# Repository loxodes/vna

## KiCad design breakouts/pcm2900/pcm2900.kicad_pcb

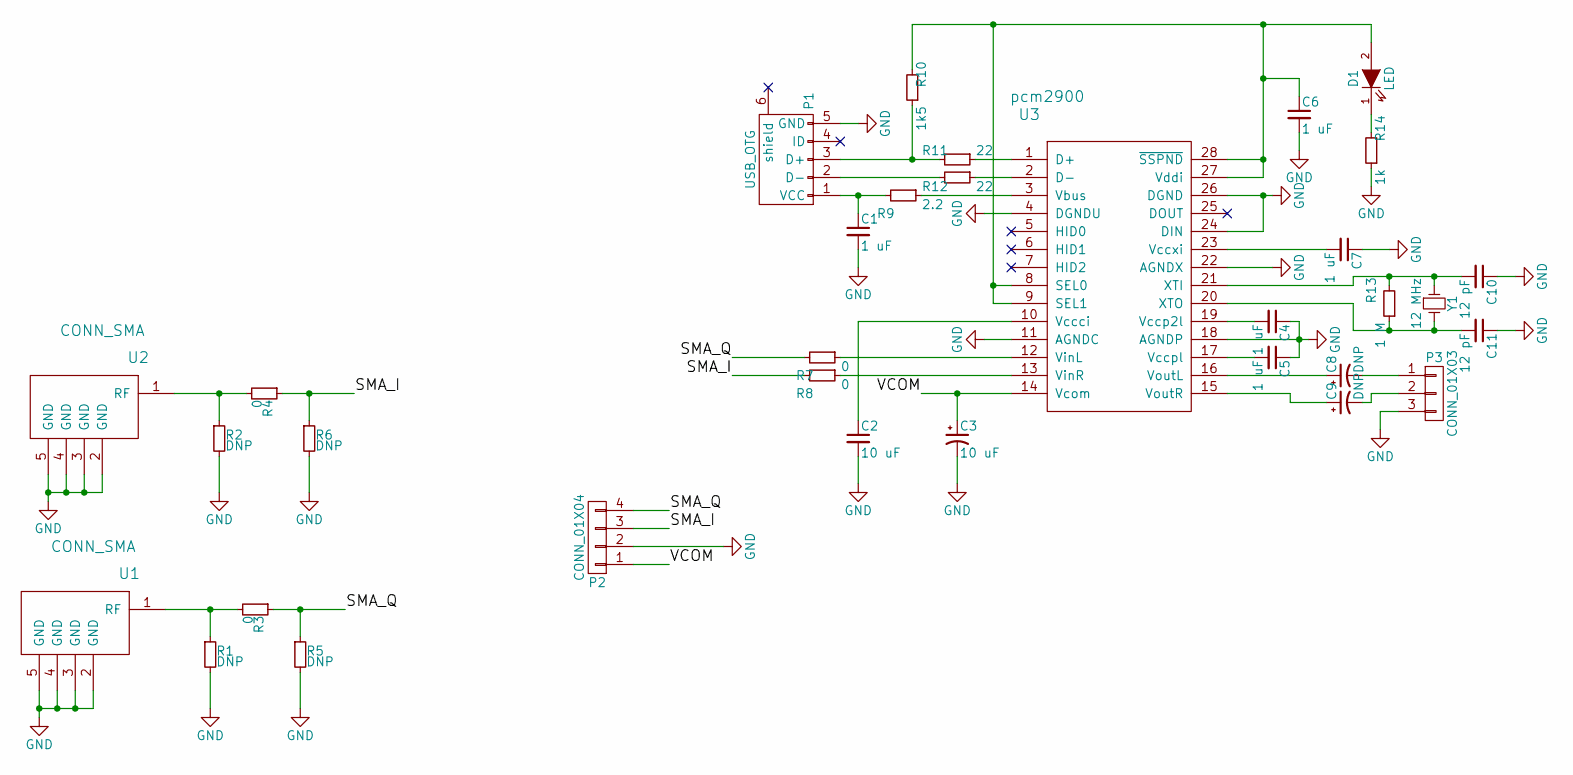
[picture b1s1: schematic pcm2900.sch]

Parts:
C1, C4, C5, C6, C7: 1 uF; C_0603
C2, C3: 10 uF; TantalC_SizeA_EIA-3216_Wave
C8, C9: DNP; TantalC_SizeA_EIA-3216_Wave
C10, C11: 12 pF; C_0603
D1: LED; LED_0603
P1: USB_OTG; USB_Mini-B
P2: CONN_01X04; Pin_Header_Straight_1x04
P3: CONN_01X03; Pin_Header_Straight_1x03
R1, R2, R5, R6: DNP; R_0603
R3, R4: 0; R_0603
R7, R8: 0; R_0805
R9: 2.2; R_0603
R10: 1k5; R_0603
R11, R12: 22; R_0603
R13: 1 M; R_0603
R14: 1k; R_0603
U1, U2: CONN_SMA; 732512200_SMA
U3: pcm2900; SSOP-28_5.3x10.2mm_Pitch0.65mm
Y1: 12 MHz; Crystal_FOX-FE_SMD

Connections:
/SMA_I: P2.3, R4.1, R6.1, R8.2
/SMA_Q: P2.4, R3.1, R5.1, R7.2
/VCOM: C3.1, P2.1, U3.14 (Vcom)
GND: C1.2, C2.2, C3.2, C4.1, C5.1, C6.2, C7.1, C10.1, C11.1, P1.5 (GND), P2.2, P3.3, R1.2, R2.2, R5.2, R6.2, R14.1, U1.2 (GND), U1.3 (GND), U1.4 (GND), U1.5 (GND), U2.2 (GND), U2.3 (GND), U2.4 (GND), U2.5 (GND), U3.4 (DGNDU), U3.11 (AGNDC), U3.18 (AGNDP), U3.22 (AGNDX), U3.24 (DIN), U3.26 (DGND)
unnamed: C1.1, P1.1 (VCC), R9.2
unnamed: C2.1, U3.10 (Vccci)
unnamed: C4.2, U3.19 (Vccp2l)
unnamed: C5.2, U3.17 (Vccpl)
unnamed: C6.1, D1.2 (A), R10.2, U3.8 (SEL0), U3.9 (SEL1), U3.27 (Vddi), U3.28 (~SSPND)
unnamed: C7.2, U3.23 (Vccxi)
unnamed: C8.1, U3.16 (VoutL)
unnamed: C8.2, P3.1
unnamed: C9.1, U3.15 (VoutR)
unnamed: C9.2, P3.2
unnamed: C10.2, R13.2, U3.21 (XTI), Y1.1
unnamed: C11.2, R13.1, U3.20 (XTO), Y1.2
unnamed: D1.1 (K), R14.2
unnamed: P1.2 (D-), R12.2
unnamed: P1.3 (D+), R10.1, R11.2
unnamed: R1.1, R3.2, U1.1 (RF)
unnamed: R2.1, R4.2, U2.1 (RF)
unnamed: R7.1, U3.12 (VinL)
unnamed: R8.1, U3.13 (VinR)
unnamed: R9.1, U3.3 (Vbus)
unnamed: R11.1, U3.1 (D+)
unnamed: R12.1, U3.2 (D-)

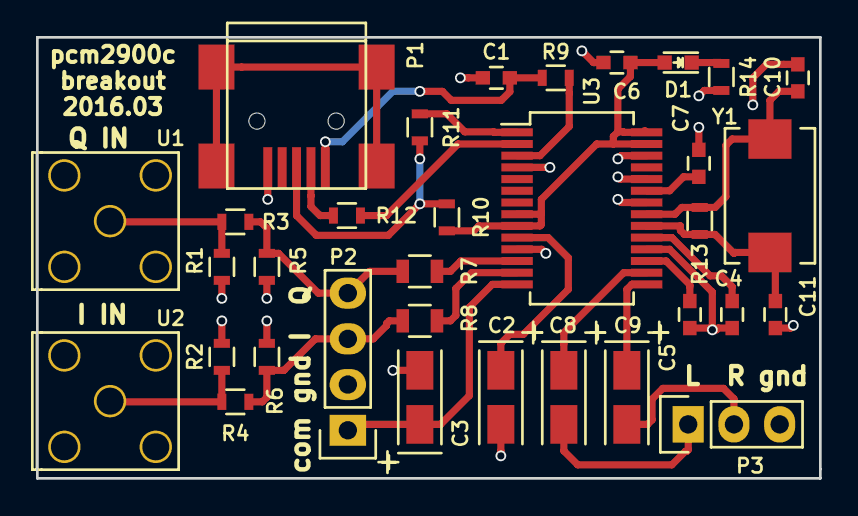
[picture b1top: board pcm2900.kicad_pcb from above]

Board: 2 copper layers, 43.5 x 24.5 mm, 33 parts (0 on the bottom side), 26 nets.

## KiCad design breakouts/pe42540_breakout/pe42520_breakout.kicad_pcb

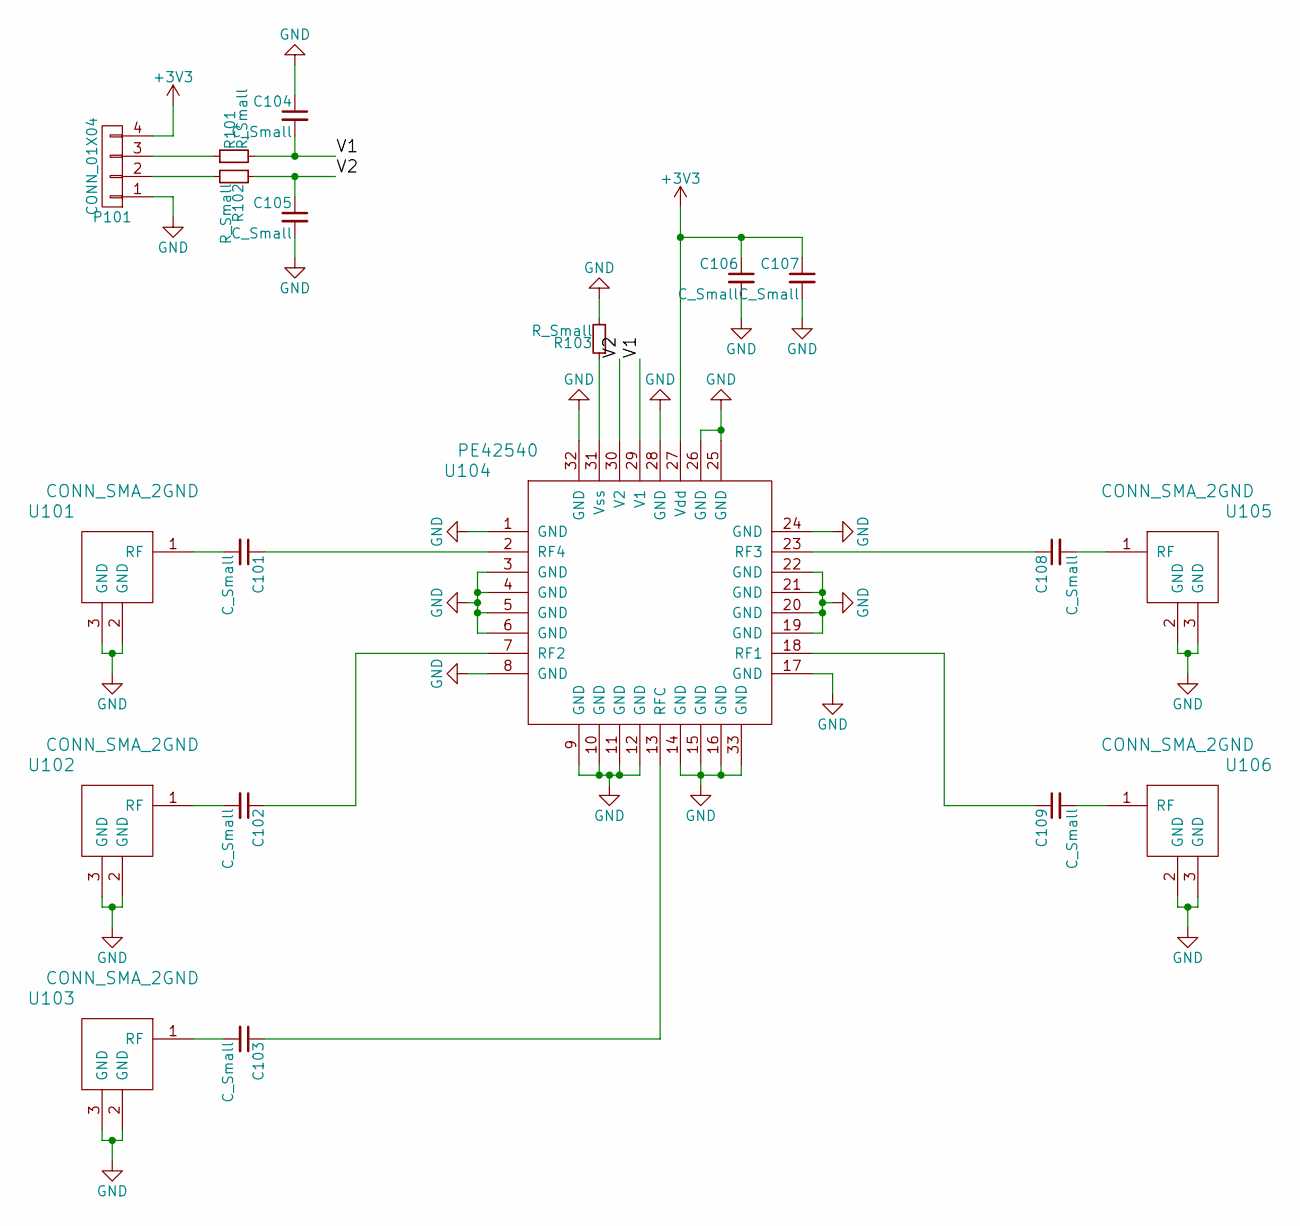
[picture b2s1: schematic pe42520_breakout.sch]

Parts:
C101, C102, C103, C104, C105, C106, C107, C108, C109: C_Small; C_0402
P101: CONN_01X04; Pin_Header_Angled_1x04
R101, R102, R103: R_Small; R_0402
U101, U102, U103, U105, U106: CONN_SMA_2GND; SMA_CPW_1MM_.2MM
U104: PE42540; LGA_32

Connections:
+3V3: C106.1, C107.1, P101.4, U104.27 (Vdd)
/V1: C104.2, R101.2, U104.29 (V1)
/V2: C105.1, R102.1, U104.30 (V2)
GND: C104.1, C105.2, C106.2, C107.2, P101.1, R103.2, U101.2 (GND), U101.3 (GND), U102.2 (GND), U102.3 (GND), U103.2 (GND), U103.3 (GND), U104.1 (GND), U104.3 (GND), U104.4 (GND), U104.5 (GND), U104.6 (GND), U104.8 (GND), U104.9 (GND), U104.10 (GND), U104.11 (GND), U104.12 (GND), U104.14 (GND), U104.15 (GND), U104.16 (GND), U104.17 (GND), U104.19 (GND), U104.20 (GND), U104.21 (GND), U104.22 (GND), U104.24 (GND), U104.25 (GND), U104.26 (GND), U104.28 (GND), U104.32 (GND), U104.33 (GND), U105.2 (GND), U105.3 (GND), U106.2 (GND), U106.3 (GND)
unnamed: C101.1, U104.2 (RF4)
unnamed: C101.2, U101.1 (RF)
unnamed: C102.1, U104.7 (RF2)
unnamed: C102.2, U102.1 (RF)
unnamed: C103.1, U104.13 (RFC)
unnamed: C103.2, U103.1 (RF)
unnamed: C108.1, U104.23 (RF3)
unnamed: C108.2, U105.1 (RF)
unnamed: C109.1, U104.18 (RF1)
unnamed: C109.2, U106.1 (RF)
unnamed: P101.2, R102.2
unnamed: P101.3, R101.1
unnamed: R103.1, U104.31 (Vss)

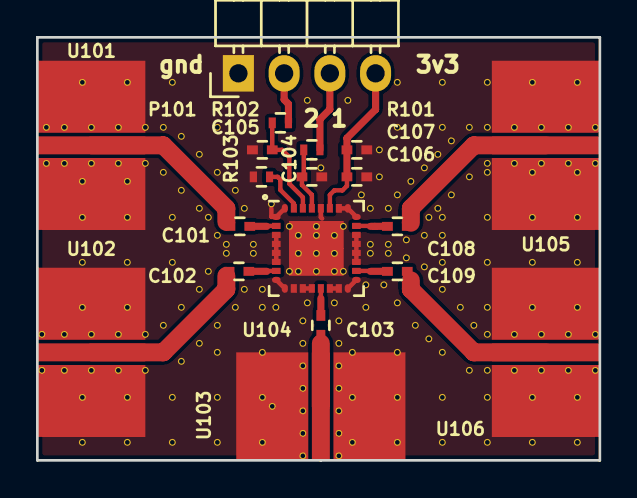
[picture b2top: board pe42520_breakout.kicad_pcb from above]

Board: 4 copper layers, 31.2 x 23.5 mm, 19 parts (0 on the bottom side), 17 nets.

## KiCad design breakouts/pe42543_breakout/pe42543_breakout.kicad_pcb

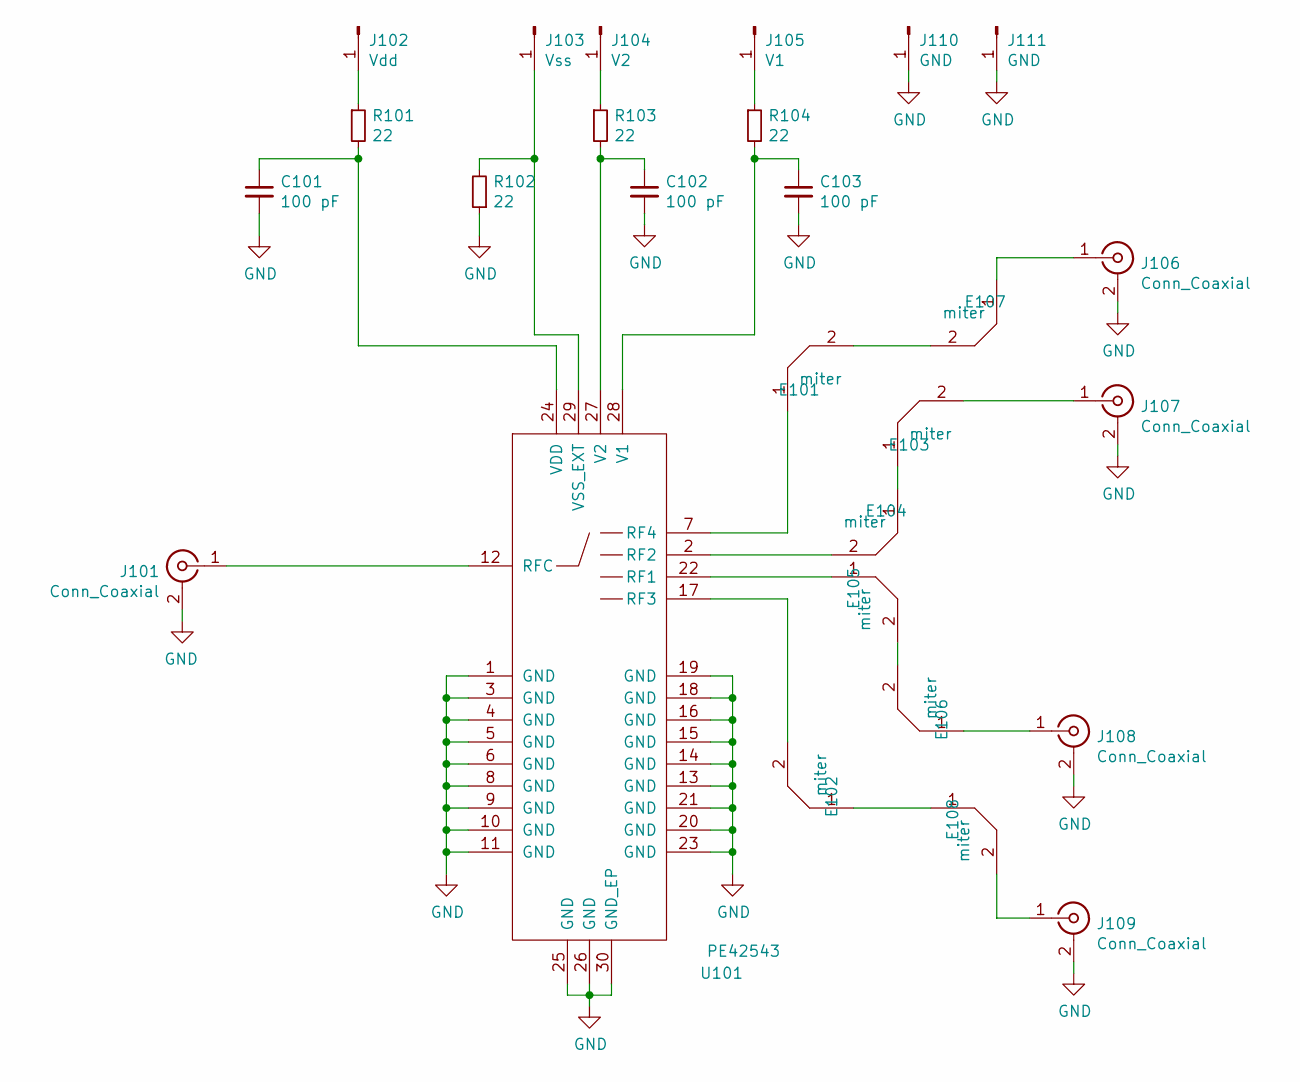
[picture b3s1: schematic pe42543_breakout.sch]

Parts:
C101, C102, C103: 100 pF; C_0402
E101, E102, E103, E104, E105, E106, E107, E108: miter; p41mm_miter
J101, J106, J107, J108, J109: Conn_Coaxial; sw_edge_oshpark_4layer
J102: Vdd; TURRET_MILLMAX_2101
J103: Vss; TURRET_MILLMAX_2101
J104: V2; TURRET_MILLMAX_2101
J105: V1; TURRET_MILLMAX_2101
J110, J111: GND; TURRET_MILLMAX_2101
R101, R102, R103, R104: 22; R_0402
U101: PE42543; RFSW__PE42543A-X

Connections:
GND: C101.2, C102.2, C103.2, J101.2 (Ext), J106.2 (Ext), J107.2 (Ext), J108.2 (Ext), J109.2 (Ext), J110.1, J111.1, R102.1, U101.1 (GND), U101.3 (GND), U101.4 (GND), U101.5 (GND), U101.6 (GND), U101.8 (GND), U101.9 (GND), U101.10 (GND), U101.11 (GND), U101.13 (GND), U101.14 (GND), U101.15 (GND), U101.16 (GND), U101.18 (GND), U101.19 (GND), U101.20 (GND), U101.21 (GND), U101.23 (GND), U101.25 (GND), U101.26 (GND), U101.30 (GND_EP)
unnamed: C101.1, R101.2, U101.24 (VDD)
unnamed: C102.1, R103.2, U101.27 (V2)
unnamed: C103.1, R104.2, U101.28 (V1)
unnamed: E101.1, U101.7 (RF4)
unnamed: E101.2, E107.2
unnamed: E102.1, E108.1
unnamed: E102.2, U101.17 (RF3)
unnamed: E103.1, E104.1
unnamed: E103.2, J107.1 (In)
unnamed: E104.2, U101.2 (RF2)
unnamed: E105.1, U101.22 (RF1)
unnamed: E105.2, E106.2
unnamed: E106.1, J108.1 (In)
unnamed: E107.1, J106.1 (In)
unnamed: E108.2, J109.1 (In)
unnamed: J101.1 (In), U101.12 (RFC)
unnamed: J102.1, R101.1
unnamed: J103.1, R102.2, U101.29 (VSS_EXT)
unnamed: J104.1, R103.1
unnamed: J105.1, R104.1

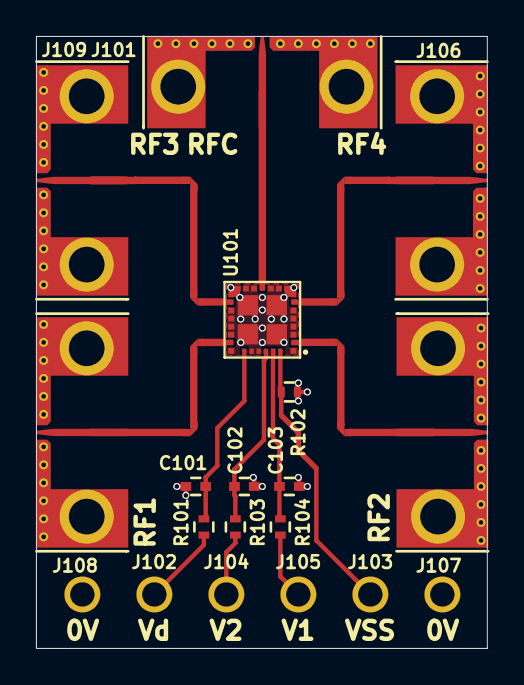
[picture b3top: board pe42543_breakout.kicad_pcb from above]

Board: 4 copper layers, 25.1 x 34.0 mm, 27 parts (0 on the bottom side), 21 nets.

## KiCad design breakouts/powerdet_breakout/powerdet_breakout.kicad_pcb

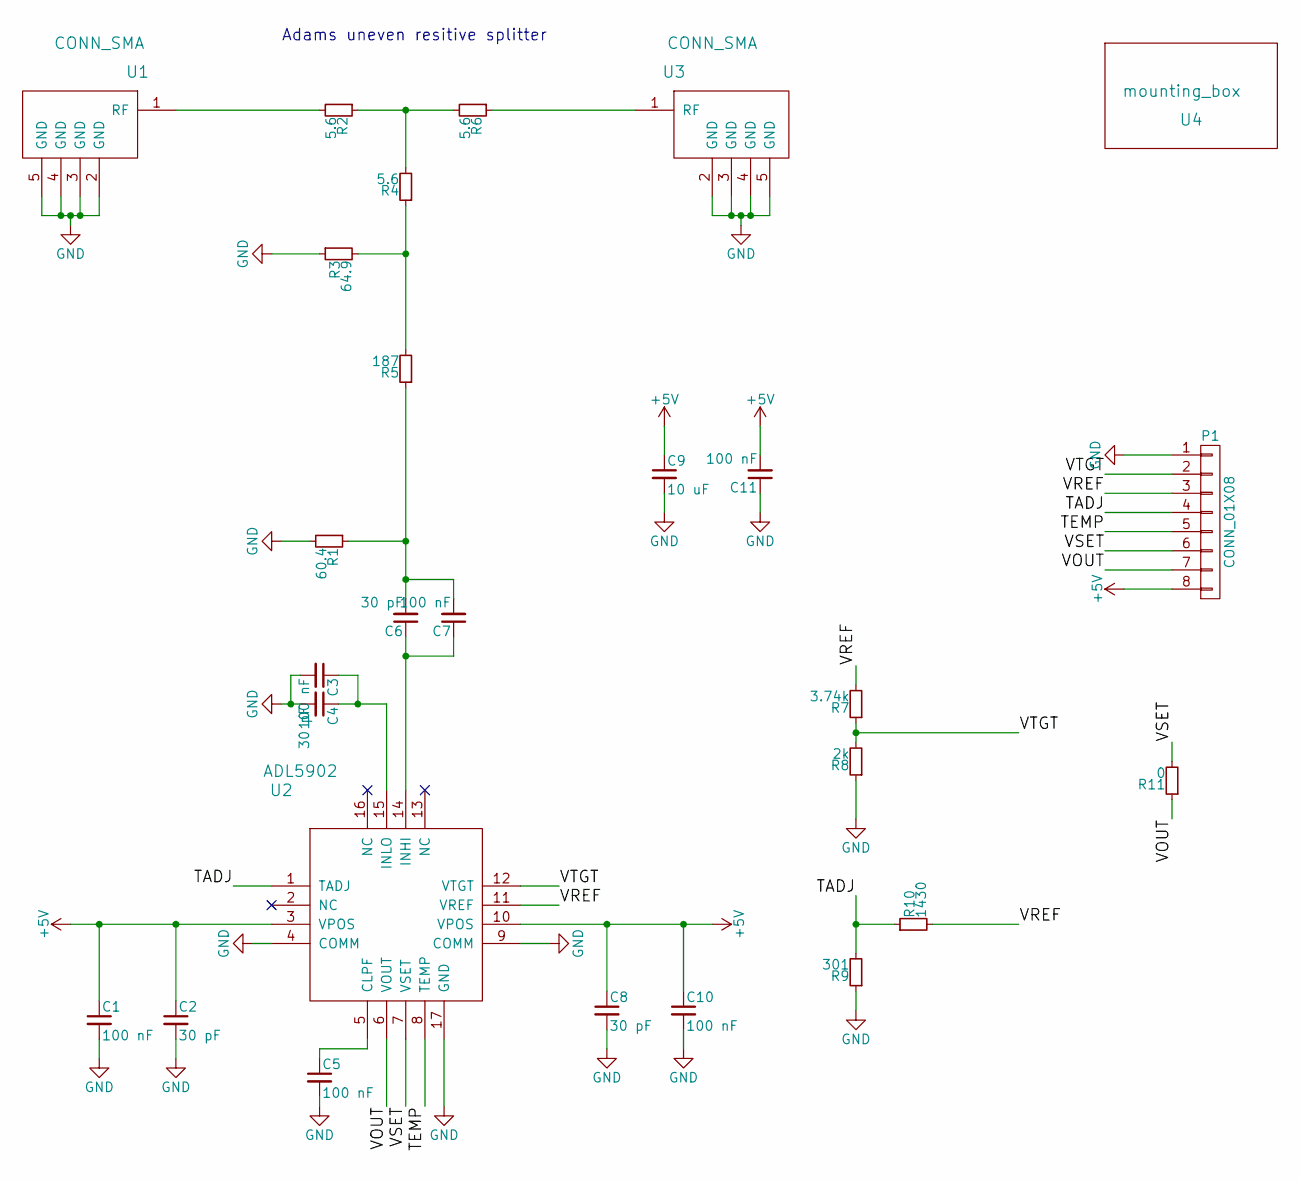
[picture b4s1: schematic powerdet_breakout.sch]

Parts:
C1, C3, C5, C7, C10, C11: 100 nF; C_0402
C2, C4, C6, C8: 30 pF; C_0402
C9: 10 uF; C_0402
P1: CONN_01X08; Pin_Header_Straight_1x08
R1: 60.4; R_0402
R2, R4, R6: 5.6; R_0402
R3: 64.9; R_0402
R5: 187; R_0402
R7: 3.74k; R_0402
R8: 2k; R_0402
R9: 301; R_0402
R10: 1430; R_0402
R11: 0; R_0402
U1, U3: CONN_SMA; 732511150_sma
U2: ADL5902; QFN-16-1EP_4x4mm_Pitch0.65mm
U4: mounting_box; POMONA_2400BOX

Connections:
+5V: C1.1, C2.1, C8.1, C9.1, C10.1, C11.2, P1.8, U2.3 (VPOS), U2.10 (VPOS)
/TADJ: P1.4, R9.2, R10.1, U2.1 (TADJ)
/TEMP: P1.5, U2.8 (TEMP)
/VOUT: P1.7, R11.1, U2.6 (VOUT)
/VREF: P1.3, R7.2, R10.2, U2.11 (VREF)
/VSET: P1.6, R11.2, U2.7 (VSET)
/VTGT: P1.2, R7.1, R8.2, U2.12 (VTGT)
GND: C1.2, C2.2, C3.2, C4.2, C5.2, C8.2, C9.2, C10.2, C11.1, P1.1, R1.2, R3.1, R8.1, R9.1, U1.2 (GND), U1.3 (GND), U1.4 (GND), U1.5 (GND), U2.4 (COMM), U2.9 (COMM), U2.17 (GND), U3.2 (GND), U3.3 (GND), U3.4 (GND), U3.5 (GND)
unnamed: C3.1, C4.1, U2.15 (INLO)
unnamed: C5.1, U2.5 (CLPF)
unnamed: C6.1, C7.1, U2.14 (INHI)
unnamed: C6.2, C7.2, R1.1, R5.1
unnamed: R2.1, R4.2, R6.2
unnamed: R2.2, U1.1 (RF)
unnamed: R3.2, R4.1, R5.2
unnamed: R6.1, U3.1 (RF)

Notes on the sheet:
Adams uneven resitive splitter

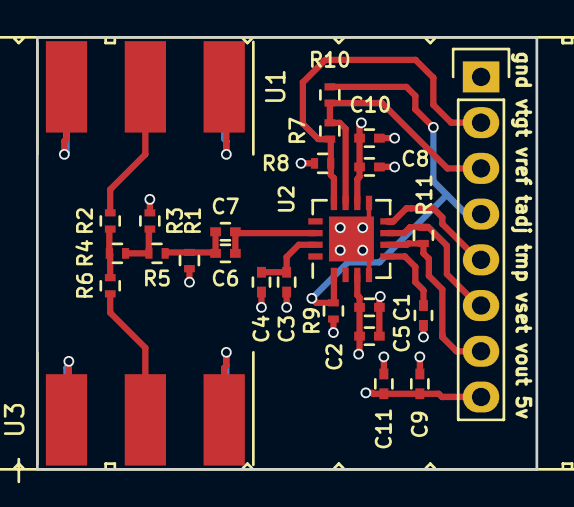
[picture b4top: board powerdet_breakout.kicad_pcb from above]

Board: 4 copper layers, 27.8 x 24.0 mm, 27 parts (0 on the bottom side), 16 nets.

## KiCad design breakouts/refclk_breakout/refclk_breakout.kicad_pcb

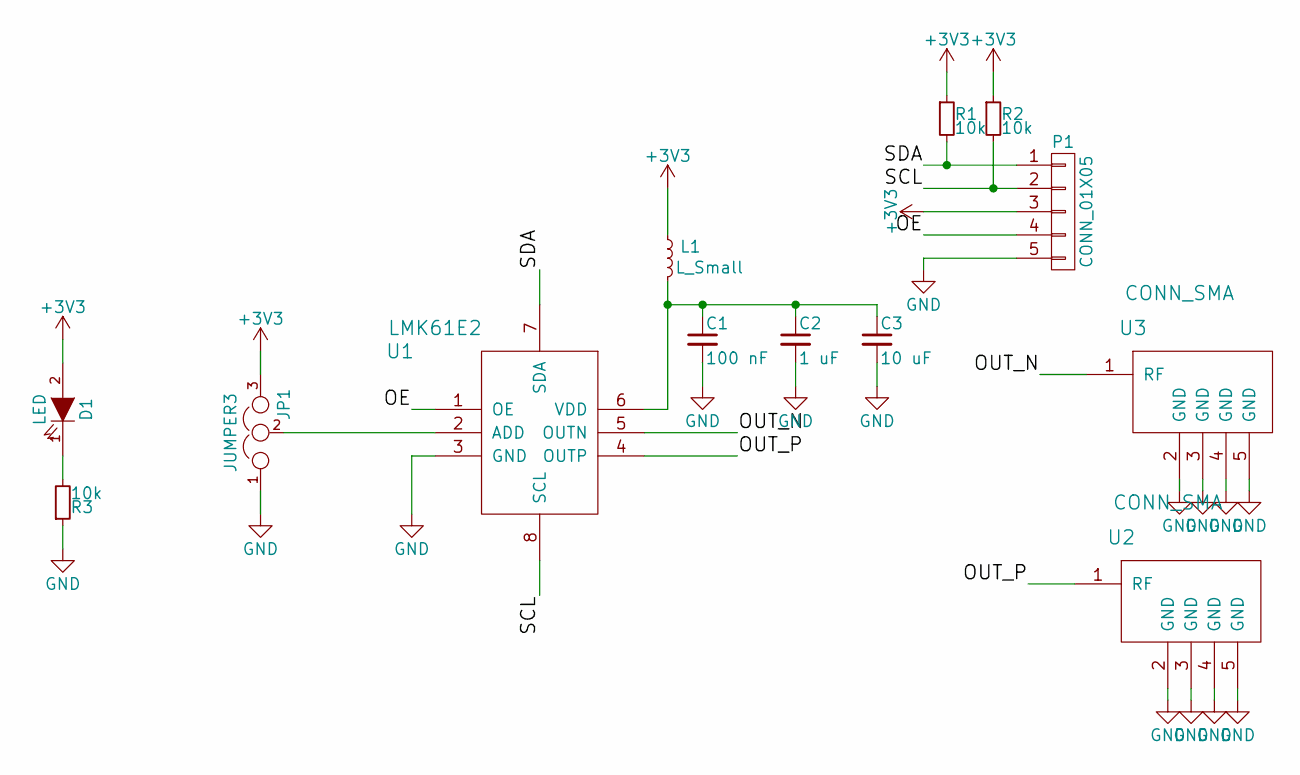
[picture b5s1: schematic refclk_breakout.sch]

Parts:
C1: 100 nF; C_0402
C2: 1 uF; C_0402
C3: 10 uF; C_0603
D1: LED; LED_0603
JP1: JUMPER3; Pin_Header_Straight_1x03
L1: L_Small; R_0603
P1: CONN_01X05; Pin_Header_Straight_1x05
R1, R2, R3: 10k; R_0402
U1: LMK61E2; QFM8
U2, U3: CONN_SMA; 732512200_SMA

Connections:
+3V3: D1.2 (A), JP1.3, L1.1, P1.3, R1.1, R2.1
/OE: P1.4, U1.1 (OE)
/OUT_N: U1.5 (OUTN), U3.1 (RF)
/OUT_P: U1.4 (OUTP), U2.1 (RF)
/SCL: P1.2, R2.2, U1.8 (SCL)
/SDA: P1.1, R1.2, U1.7 (SDA)
GND: C1.2, C2.2, C3.2, JP1.1, P1.5, R3.1, U1.3 (GND), U2.2 (GND), U2.3 (GND), U2.4 (GND), U2.5 (GND), U3.2 (GND), U3.3 (GND), U3.4 (GND), U3.5 (GND)
unnamed: C1.1, C2.1, C3.1, L1.2, U1.6 (VDD)
unnamed: D1.1 (K), R3.2
unnamed: JP1.2, U1.2 (ADD)

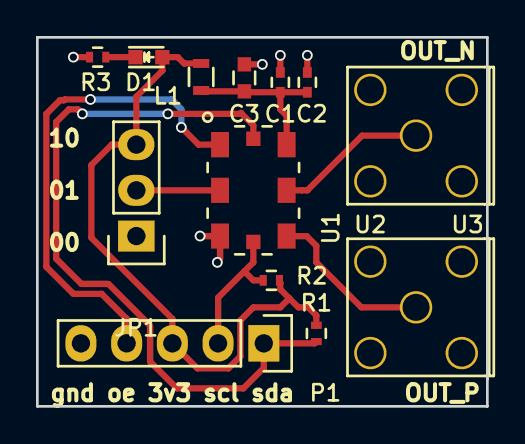
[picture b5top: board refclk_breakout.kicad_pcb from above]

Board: 4 copper layers, 25.0 x 20.5 mm, 13 parts (0 on the bottom side), 10 nets.

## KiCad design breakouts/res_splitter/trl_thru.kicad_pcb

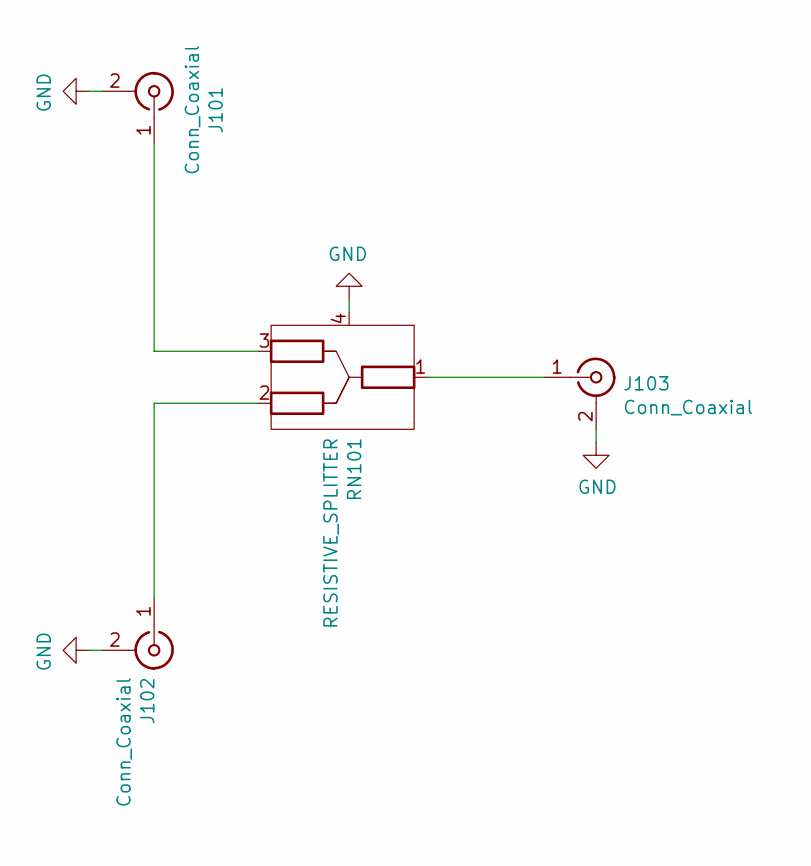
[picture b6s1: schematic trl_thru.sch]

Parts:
J101, J102, J103: Conn_Coaxial; sw_edge_oshpark_4layer
RN101: RESISTIVE_SPLITTER; PDR06380

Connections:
GND: J101.2 (Ext), J102.2 (Ext), J103.2 (Ext), RN101.4
unnamed: J101.1 (In), RN101.3
unnamed: J102.1 (In), RN101.2
unnamed: J103.1 (In), RN101.1

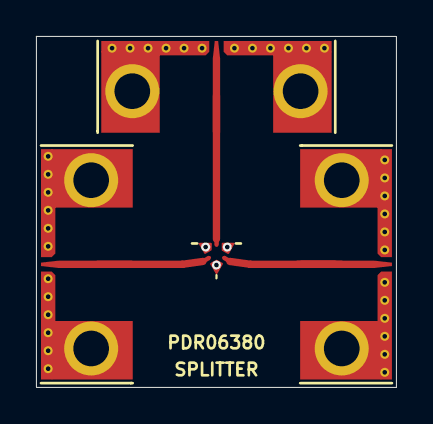
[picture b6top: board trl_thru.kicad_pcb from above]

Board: 4 copper layers, 20.0 x 19.5 mm, 4 parts (0 on the bottom side), 4 nets.

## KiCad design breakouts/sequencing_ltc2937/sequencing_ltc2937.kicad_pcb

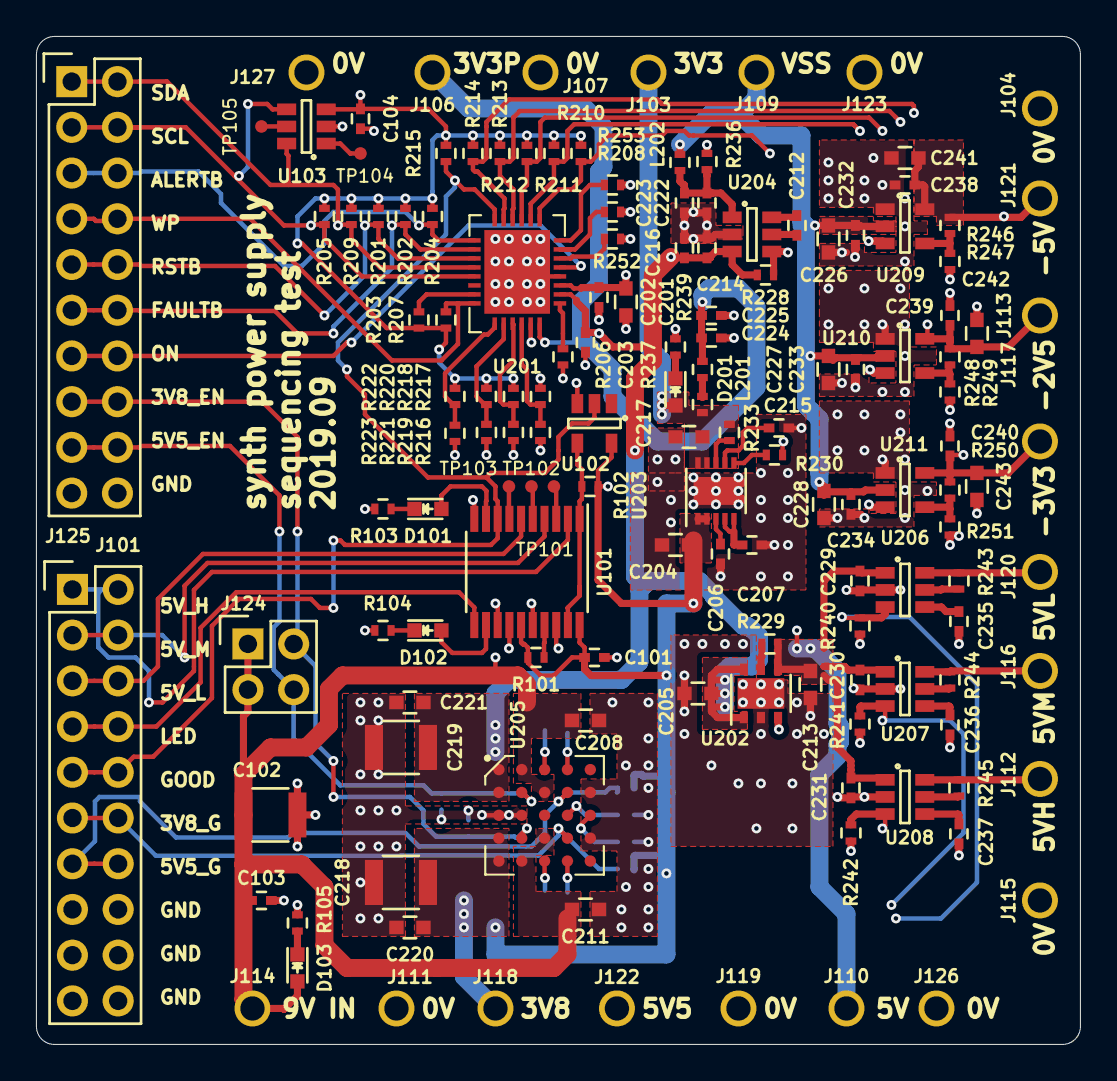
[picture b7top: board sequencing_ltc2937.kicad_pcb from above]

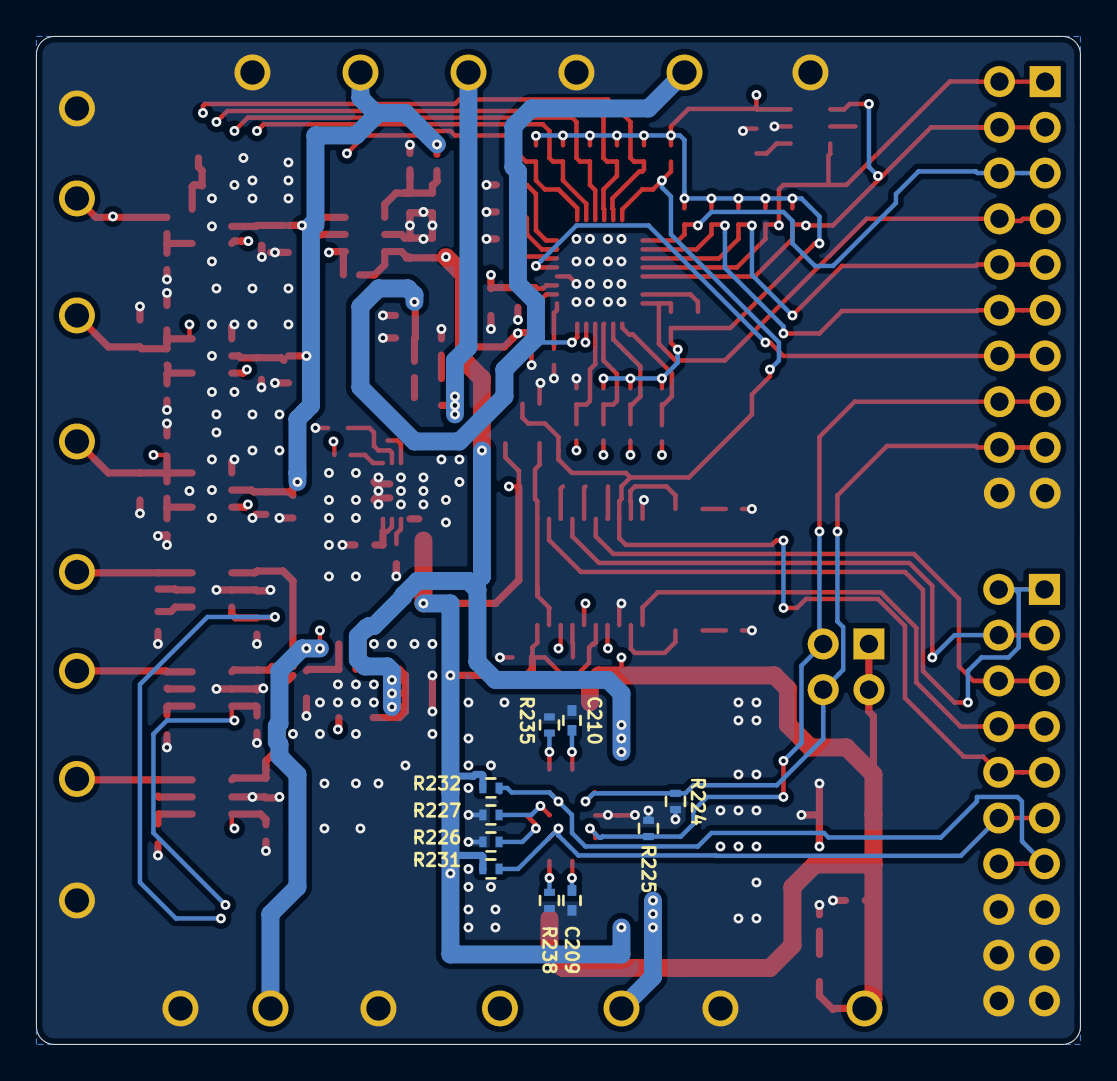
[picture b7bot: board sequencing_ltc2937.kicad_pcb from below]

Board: 4 copper layers, 58.0 x 56.0 mm, 153 parts (10 on the bottom side), 87 nets.

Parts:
C101, C104, C202, C203, C209, C210, C214, C222, C225, C232, C233, C234: 100 nF; C_0402
C102, C218, C219: 47 uF; C_1210
C103, C206, C207, C212, C215, C216, C223, C224, C229, C230, C231: 1 uF; C_0402
C201, C205, C213, C220, C221, C226, C227, C228, C241, C242, C243: 2.2 uF; C_0603
C204, C208, C211, C217: 10 uF; C_0603
C235, C236, C237: DNI; C_0402
C238, C239, C240: 10 nF; C_0402
D101, D102, D103, D201: LED_Small; LED_0603
J101, J125: Conn_02x10_Odd_Even; Pin_Header_Straight_2x10
J103, J106: 3.3VP; TURRET_MILLMAX_2101
J104, J107, J111, J115, J119, J123, J126, J127: GND; TURRET_MILLMAX_2101
J109: VSS; TURRET_MILLMAX_2101
J110: +5VP; TURRET_MILLMAX_2101
J112: VX2; TURRET_MILLMAX_2101
J113: -2V5; TURRET_MILLMAX_2101
J114: +9V; TURRET_MILLMAX_2101
J116: VAMP_MID; TURRET_MILLMAX_2101
J117: -3V3; TURRET_MILLMAX_2101
J118: +3V8; TURRET_MILLMAX_2101
J120: VAMP_LOW; TURRET_MILLMAX_2101
J121: -5V; TURRET_MILLMAX_2101
J122: +6V; TURRET_MILLMAX_2101
J124: Conn_02x02_Odd_Even; Pin_Header_Straight_2x02
L201, L202: BLM15GG471; R_0402
R101, R102, R103, R104, R105, R203, R205, R207, R209, R210, R211, R212, R213, R214, R215, R218, R220, R222, R224, R225, R231, R232, R237, R240, R241, R242: 10k; R_0402
R201, R202, R204, R216: 100k; R_0402
R206, R208, R226, R227, R236, R252, R253: DNI; R_0402
R217, R248: 51k; R_0402
R219, R221, R247: 21k; R_0402
R223, R249: 47k; R_0402
R228, R230, R243, R244, R245: 1k; R_0402
R229, R233: 0; R_0402
R235: 7.5k; R_0402
R238: 12k; R_0402
R239: 10; R_0402
R246, R250: 68k; R_0402
R251: 39k; R_0402
TP101: 3V8_WEAK; TP07R
TP102: 3V8; TP07R
TP103: GND; TP07R
TP104: ADDR; TP07R
TP105: ALERT; TP07R
U101: 74HC244; TSSOP-20_4.4x6.5mm_Pitch0.65mm
U102: 74xx1G14; SOT-23-5
U103: LM73; SOT-23-6
U201: LTC2937; QFN-28_EP_6x5_Pitch0.5mm
U202: NCP692; DFN-6-1EP_3x3mm_Pitch0.95mm
U203: ADP7158; DFN-10-1EP_3x3mm_Pitch0.5mm
U204: LM2776; SOT-23-6
U205: LTM4622A; BGA-25_5x5_6.35x6.35mm
U206, U207, U208: TPS22918; SOT-23-6
U209, U210, U211: TPS72301DB; SOT-23-5

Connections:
+3.3VP: C224.2, C225.2, J106.1, R239.2, U201.28
+3V3: C217.2, D201.2, J103.1, L201.1, R233.1, U203.9, U203.10
+3V8: C101.1, C204.2, C218.1, C220.1, J118.1, R101.1, R102.1, R231.2, R232.2, U101.15, U101.20, U102.5, U203.1, U203.2, U205.D1, U205.E1
+5VP: C213.2, C229.1, C230.1, C231.1, J110.1, R229.2, U201.27, U202.4, U206.1, U207.1, U208.1
+6V: C203.2, C205.2, C214.2, C216.2, C219.1, C221.1, J122.1, R228.1, U201.2, U202.1, U202.6, U204.3, U205.A1, U205.B1
+9V: C102.1, C103.1, C208.1, C211.1, D103.2, J114.1, J124.1, J124.3, R216.1, U205.A2, U205.B3, U205.D3, U205.E2
-2V5: C239.1, C242.1, J113.1, R219.1, R248.1, U210.5
-3V3: C240.1, C243.1, J117.1, R221.1, R250.1, U211.5
-5V: C238.1, C241.1, J121.1, R223.1, R246.1, U209.5
/3V8_EN: J124.2, J125.15, J125.16, R225.1, U205.D2
/5V5_EN: J124.4, J125.17, J125.18, R224.1, U205.B2
/ALERTB: J125.5, J125.6, R204.2, U201.15
/FAULTB: J125.11, J125.12, R202.2, U201.16
/HIGHBAND_CONN: J101.1, J101.2, U101.2
/HIGHBAND_EN: R242.1, U101.18, U208.3
/HIGHBAND_VX2: J112.1, R245.2, U208.6
/LED_CONN: J101.7, J101.8, U101.11
/LOWBAND_CONN: J101.5, J101.6, U101.6
/LOWBAND_EN: R240.1, U101.14, U206.3
/LOWBAND_VAMP: J120.1, R243.2, U206.6
/MIDBAND_CONN: J101.3, J101.4, U101.4
/MIDBAND_EN: R241.1, U101.16, U207.3
/MIDBAND_VAMP: J116.1, R244.2, U207.6
/ON: J125.13, J125.14, U201.5
/PGOOD_3V8: J101.11, J101.12, R231.1, U205.D4
/PGOOD_5V5: J101.13, J101.14, R232.1, U205.B4
/PGOOD_ALL: J101.9, J101.10, R215.1, U101.8, U102.2, U201.14
/PGOOD_INV: R102.2, U101.1, U101.19, U102.4
/PGOOD_LED: D102.2, U101.12
/PMIC_3V3: C104.1, C201.1, C202.1, R201.1, R202.1, R203.1, R204.1, R205.1, R207.2, R209.1, R210.2, R211.2, R212.2, R213.2, R214.2, R215.2, R218.1, R220.1, R222.1, U103.3, U201.3
/PMIC_SCL: J125.3, J125.4, R205.2, U103.4, U201.19
/PMIC_SDA: J125.1, J125.2, R209.2, U103.6, U201.18
/RSTB: J125.9, J125.10, R201.2, U201.17
/WP: J125.7, J125.8, R203.2, U201.22
/amp_bias/3V3_EN: R213.1, R230.1, U201.12
/amp_bias/5V_EN: R214.1, U201.13, U202.3
/amp_bias/M2_5V_EN: R211.1, U201.10, U210.3
/amp_bias/M3_5V_EN: R212.1, U201.11, U211.3
/amp_bias/M5V_EN: R210.1, U201.9, U209.3
GND: C101.2, C102.2, C103.2, C104.2, C201.2, C202.2, C203.1, C204.1, C205.1, C206.1, C207.1, C208.2, C209.2, C210.2, C211.2, C213.1, C214.1, C215.1, C216.1, C217.1, C218.2, C219.2, C220.2, C221.2, C222.1, C223.1, C224.1, C225.1, C226.2, C227.2, C228.2, C229.2, C230.2, C231.2, C232.2, C233.2, C234.2, C235.2, C236.2, C237.2, C238.2, C239.2, C240.2, C241.2, C242.2, C243.2, J101.15, J101.16, J101.17, J101.18, J101.19, J101.20, J104.1, J107.1, J111.1, J115.1, J119.1, J123.1, J125.19, J125.20, J126.1, J127.1, R103.2, R104.2, R105.2, R206.2, R208.2, R217.1, R224.2, R225.2, R226.1, R227.1, R235.2, R236.2, R237.1, R238.2, R240.2, R241.2, R242.2, R247.2, R249.2, R251.2, R252.2, R253.2, U101.10, U101.13, U102.3, U103.2, U201.4, U201.29, U202.2, U202.7, U203.11, U204.2, U205.B5, U205.C1, U205.C2, U205.D5, U206.2, U207.2, U208.2, U209.1, U210.1, U211.1
unnamed: C206.2, U203.3
unnamed: C207.2, U203.4, U203.5
unnamed: C209.1, U205.E3
unnamed: C210.1, U205.A3
unnamed: C212.1, U204.6
unnamed: C212.2, U204.5
unnamed: C215.2, U203.7
unnamed: C222.2, C223.2, L202.2, R236.1, U204.1
unnamed: C235.1, U206.4
unnamed: C236.1, U207.4
unnamed: C237.1, U208.4
unnamed: D101.1, R103.1
unnamed: D101.2, U101.9
unnamed: D102.1, R104.1
unnamed: D103.1, R105.1
unnamed: D201.1, R237.2
unnamed: L201.2, R239.1
unnamed: R101.2, U101.17
unnamed: R206.1, U201.1
unnamed: R207.1, U201.21
unnamed: R208.1, U201.7
unnamed: R216.2, R217.2, U201.26
unnamed: R218.2, R219.2, U201.25
unnamed: R220.2, R221.2, U201.24
unnamed: R222.2, R223.2, U201.23
unnamed: R226.2, U205.C5
unnamed: R227.2, U205.C4
unnamed: R228.2, U204.4
unnamed: R229.1, U202.5
unnamed: R230.2, U203.6
unnamed: R233.2, U203.8
unnamed: R235.1, U205.A4
unnamed: R238.1, U205.E4
unnamed: R243.1, U206.5
unnamed: R244.1, U207.5
unnamed: R245.1, U208.5
unnamed: R246.2, R247.1, U209.4
unnamed: R248.2, R249.1, U210.4
unnamed: R250.2, R251.1, U211.4
unnamed: R252.1, U201.6
unnamed: R253.1, U201.8
unnamed: TP101.1, U101.3
unnamed: TP102.1, U101.5
unnamed: TP103.1, U101.7
unnamed: TP104.1, U103.1
unnamed: TP105.1, U103.5
VSS: C226.1, C227.1, C228.1, C232.1, C233.1, C234.1, J109.1, L202.1, U209.2, U210.2, U211.2

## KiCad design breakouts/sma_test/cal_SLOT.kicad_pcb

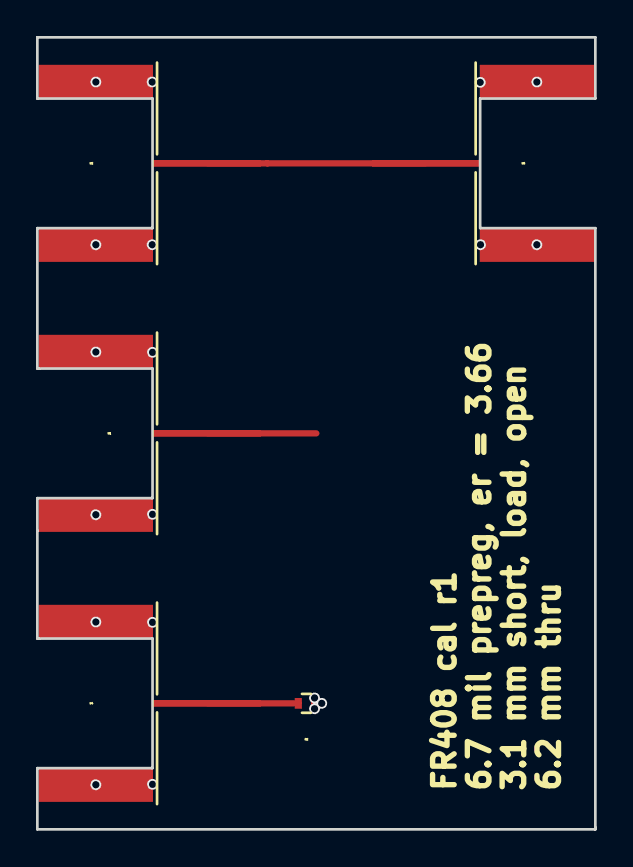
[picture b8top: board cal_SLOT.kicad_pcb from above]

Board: 4 copper layers, 31.0 x 44.0 mm, 5 parts (0 on the bottom side), 3 nets.

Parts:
R2: 0; R_0402
U1, U2, U4, U5: CONN_SMA; 142-0721-882_sma_cutout

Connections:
GND: R2.1, U1.2, U1.3, U2.2, U2.3, U4.2, U4.3, U5.2, U5.3
unnamed: R2.2, U4.1
unnamed: U2.1, U5.1
